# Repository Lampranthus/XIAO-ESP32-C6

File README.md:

# XIAO-ESP32-C6

queremos enviar los datos de la esp en un txt a a nube, por el momento a google drive por una api.

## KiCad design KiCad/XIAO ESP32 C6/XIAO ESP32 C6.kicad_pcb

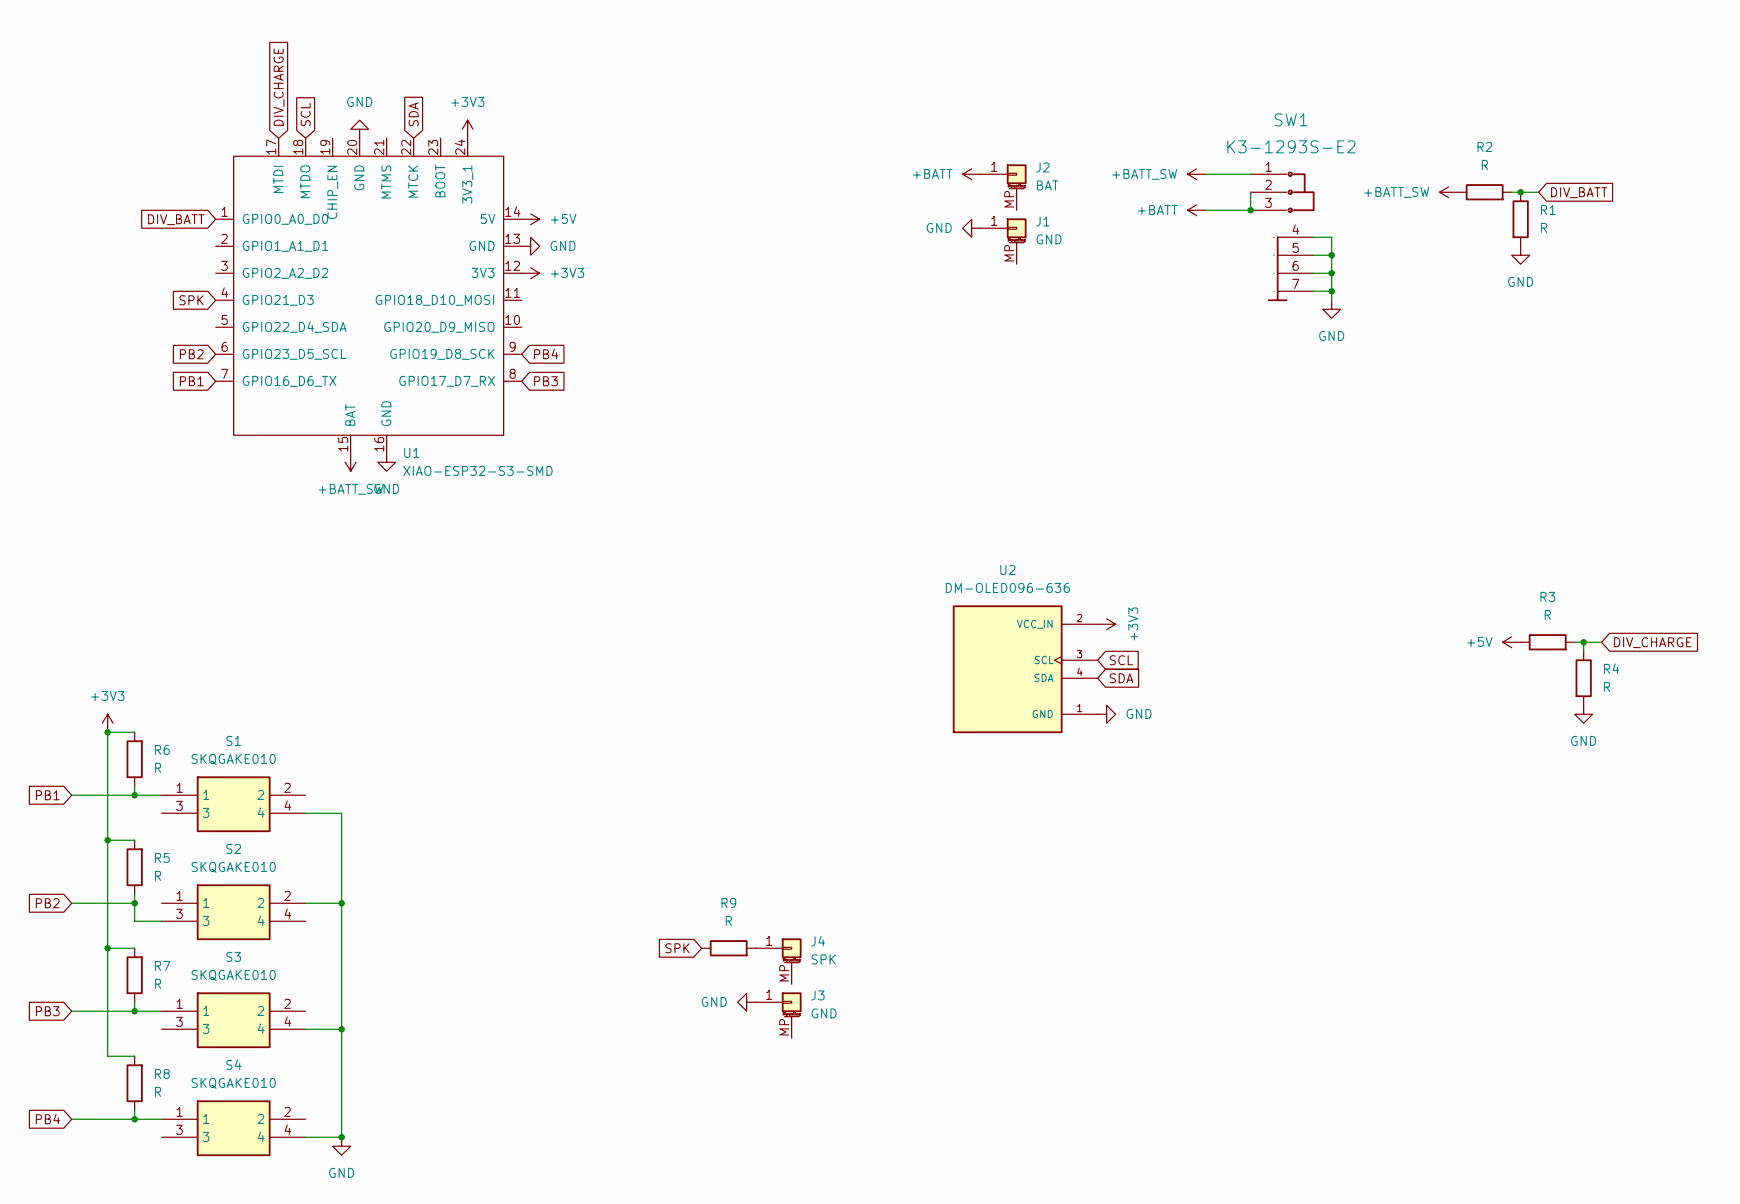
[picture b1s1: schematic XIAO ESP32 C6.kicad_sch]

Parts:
J1, J3: GND; TestPoint_Pad_1.5x1.5mm
J2: BAT; TestPoint_Pad_D1.5mm
J4: SPK; TestPoint_Pad_D1.5mm
R1, R2, R3, R4, R5, R6, R7, R8, R9: R; R_0805_2012Metric_Pad1.20x1.40mm_HandSolder
S1, S2, S3, S4: SKQGAKE010; Mouser Part Number 688-SKQGAKE010
SW1: K3-1293S-E2; SW-TH_K3-1293S-E2; Manufacturer Part K3-1293S-E2
U1: XIAO-ESP32-S3-SMD; XIAO-ESP32C6-SMD
U2: DM-OLED096-636; MODULE_DM-OLED096-636; PARTREV 2018-09-10

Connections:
+3V3: R5.2, R6.2, R7.2, R8.2, U1.12 (3V3), U1.24 (3V3_1), U2.2 (VCC_IN)
+5V: R3.1, U1.14 (5V)
+BATT: J2.1, SW1.2, SW1.3
+BATT_SW: R2.1, SW1.1, U1.15 (BAT)
DIV_BATT: R1.1, R2.2, U1.1 (GPIO0_A0_D0)
DIV_CHARGE: R3.2, R4.1, U1.17 (MTDI)
GND: J1.1, J3.1, R1.2, R4.2, S1.4, S2.2, S3.4, S4.4, SW1.4, SW1.5, SW1.6, SW1.7, U1.13 (GND), U1.16 (GND), U1.20 (GND), U2.1 (GND)
unnamed: J4.1, R9.2
PB1: R6.1, S1.1, U1.7 (GPIO16_D6_TX)
PB2: R5.1, S2.3, U1.6 (GPIO23_D5_SCL)
PB3: R7.1, S3.1, U1.8 (GPIO17_D7_RX)
PB4: R8.1, S4.1, U1.9 (GPIO19_D8_SCK)
SCL: U1.18 (MTDO), U2.3 (SCL)
SDA: U1.22 (MTCK), U2.4 (SDA)
SPK: R9.1, U1.4 (GPIO21_D3)

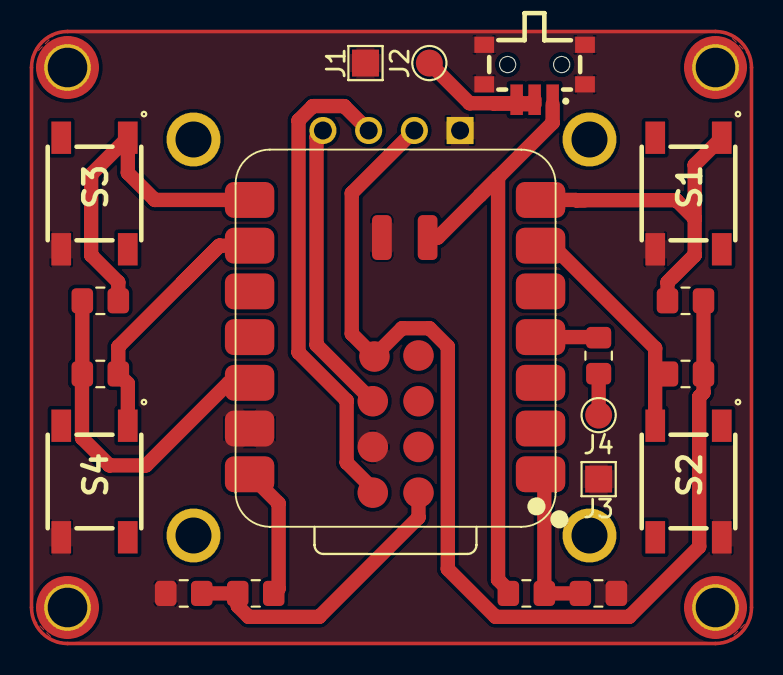
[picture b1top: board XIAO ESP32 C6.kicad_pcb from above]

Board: 2 copper layers, 20 parts (1 on the bottom side), 15 nets.

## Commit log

2025-02-25 credenciales api - no concluido
2025-03-05 version 0.1 - primera pcb
2025-03-05 Added sensitive files to .gitignore
